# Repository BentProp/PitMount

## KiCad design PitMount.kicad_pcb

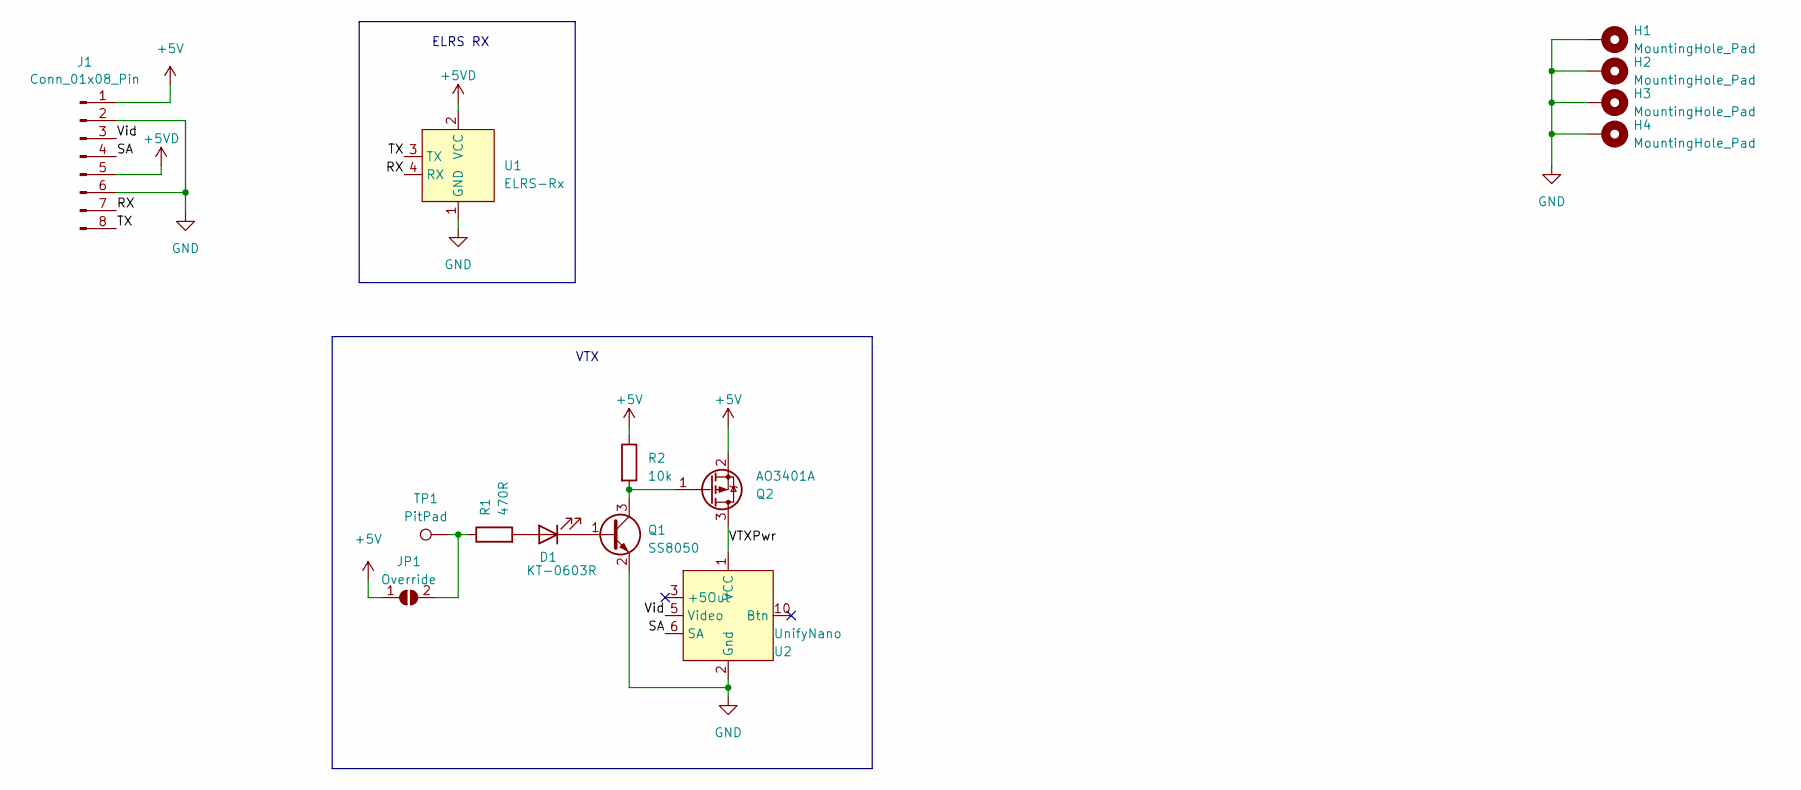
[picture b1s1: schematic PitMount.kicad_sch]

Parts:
D1: KT-0603R; LED_0603_1608Metric; LCSC C2286
H1, H2, H3, H4: MountingHole_Pad; 3.2mm_PTH
J1: Conn_01x08_Pin; VTXConn
JP1: Override; SolderJumper-2_P1.3mm_Open_RoundedPad1.0x1.5mm
Q1: SS8050; SOT-23; LCSC C2150
Q2: AO3401A; SOT-23; LCSC C15127
R1: 470R; R_0402_1005Metric; LCSC C25117
R2: 10k; R_0402_1005Metric; LCSC C25744
TP1: PitPad; TestPoint_Pad_1.5x1.5mm
U1: ELRS-Rx
U2: UnifyNano

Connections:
+5V: J1.1, JP1.1 (A), Q2.2 (S), R2.1
+5VD: J1.5, U1.2 (VCC)
/RX: J1.7, U1.4 (RX)
/SA: J1.4, U2.6 (SA)
/TX: J1.8, U1.3 (TX)
/VTXPwr: Q2.3 (D), U2.1 (VCC)
/Vid: J1.3, U2.5 (Video)
GND: H1.1, H2.1, H3.1, H4.1, J1.2, J1.6, Q1.2 (E), U1.1 (GND), U2.2 (Gnd), U2.4 (Gnd), U2.7 (Gnd), U2.8 (Gnd), U2.9 (Gnd)
unnamed: D1.2 (A), R1.2
unnamed: D1.1 (K), Q1.1 (B)
unnamed: JP1.2 (B), R1.1, TP1.1
unnamed: Q1.3 (C), Q2.1 (G), R2.2

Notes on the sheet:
VTX
ELRS RX

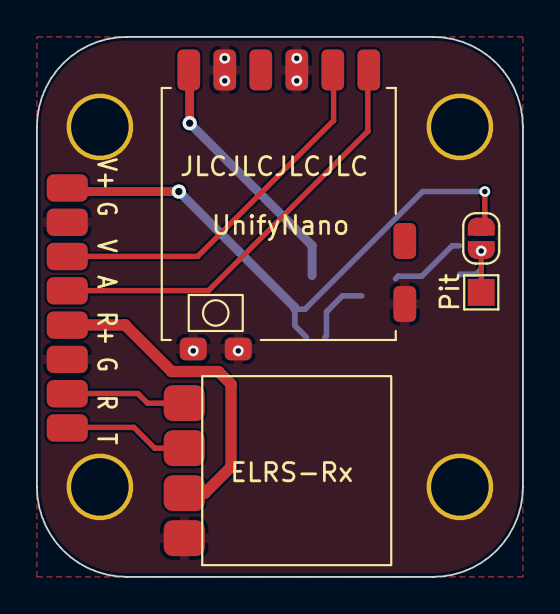
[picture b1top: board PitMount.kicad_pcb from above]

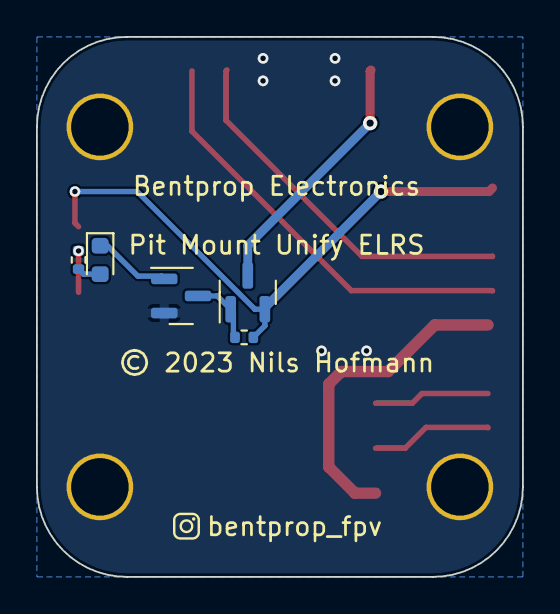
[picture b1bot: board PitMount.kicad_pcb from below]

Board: 2 copper layers, 27.0 x 30.0 mm, 14 parts (5 on the bottom side), 12 nets.

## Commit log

2023-01-13 Add footprints for user-defined parts
2023-01-13 Add gitignore
2023-01-13 Add schematics for user-defined parts
2023-01-13 Add initial project files
2023-01-17 Add simple 3.2mm PTH without pad
2023-01-17 Fix resistor LCSC reference
2023-01-17 Use new mounting hole footprint
2023-01-17 Make LED a 0402 component
2023-01-17 Update PCB with new footprints
2023-01-17 Ignore out-folder
2023-01-17 Add footprint for tooling holes
2023-01-17 Add schematics for tooling holes
2023-01-17 Add tooling holes to schematics
2023-01-17 Add tooling holes to PCB
2023-01-17 Change resistor type
2023-01-17 Change LED type
2023-01-18 Update project files with version 7.0-rc1
2023-01-18 Fix mounting hole drawing
2023-01-18 Use updated mounting hole in PCB
2023-01-18 Fix DRC rules
2023-01-18 Fix silkscreen issues
2023-01-18 Fix JLC wants silkscreen - mask
2023-01-18 Update xml output
2023-01-19 Update ELRS-Rx footprint
2023-01-19 Fix default via size
2023-01-19 Update schematic file
    - Change solder connector to 8-pin
    - Change footprint of LED to 0603
    - Use basic parts where possible
    - Compact FET drawing
    - Remove tooling holes
2023-01-19 Add title block to schematic and PCB sheets
2023-01-19 Update XML export file
2023-01-19 Change gerber export settings to JLC values
2023-01-19 Update PCB layout
2023-01-19 Exclude non-mounted parts from BOM
2023-01-19 Add production files to repository
2023-01-23 Exclude non-populatable symbols from BOM
2023-02-02 Add insta logo to footprint library
2023-02-02 Switch to an n-channel FET
2023-02-02 Update fabrication files
2023-02-03 Fix sheet comments
2023-02-07 Enlarge courtyard to allow for hex nuts
2023-02-07 Update symbol drawings
2023-02-07 Update schematic with npn bjt and p-channel mosfet
2023-02-08 Update PCB drawing

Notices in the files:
PitMount.kicad_pcb:
© 2023 Nils Hofmann
